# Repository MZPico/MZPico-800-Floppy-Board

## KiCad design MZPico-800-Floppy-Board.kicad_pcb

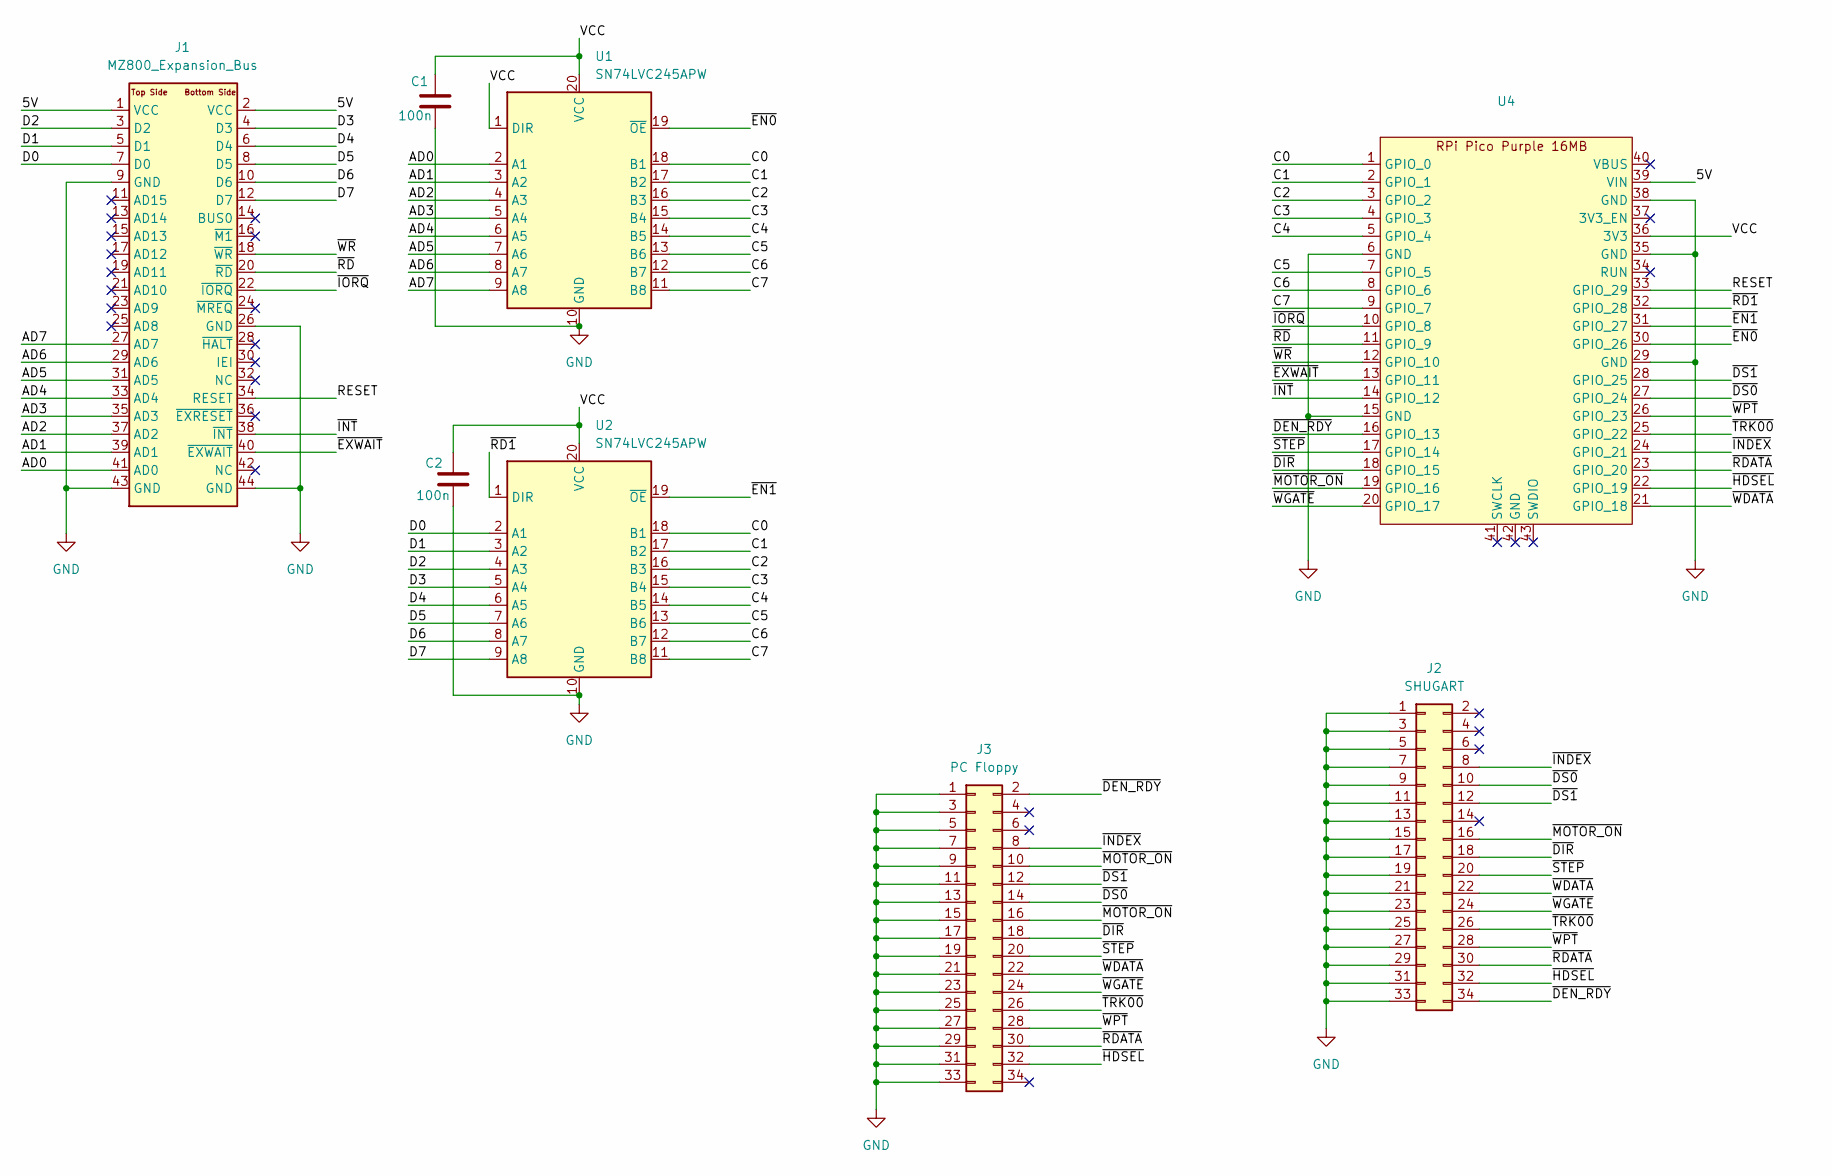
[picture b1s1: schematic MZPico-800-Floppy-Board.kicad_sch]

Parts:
C1, C2: 100n; C_0805_2012Metric
J1: MZ800_Expansion_Bus; MZ800_Expansion_Edge
J2: SHUGART; Floppy_Shugart_Edge
J3: PC Floppy; IDC-Header_2x17_P2.54mm_Horizontal
U1, U2: SN74LVC245APW; TSSOP-20_4.4x6.5mm_P0.65mm
U4: Pico_Purple_16MB

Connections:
/5V: J1.1 (VCC), J1.2 (VCC), U4.39 (VIN)
/AD0: J1.41 (AD0), U1.2 (A1)
/AD1: J1.39 (AD1), U1.3 (A2)
/AD2: J1.37 (AD2), U1.4 (A3)
/AD3: J1.35 (AD3), U1.5 (A4)
/AD4: J1.33 (AD4), U1.6 (A5)
/AD5: J1.31 (AD5), U1.7 (A6)
/AD6: J1.29 (AD6), U1.8 (A7)
/AD7: J1.27 (AD7), U1.9 (A8)
/C0: U1.18 (B1), U2.18 (B1), U4.1 (GPIO_0)
/C1: U1.17 (B2), U2.17 (B2), U4.2 (GPIO_1)
/C2: U1.16 (B3), U2.16 (B3), U4.3 (GPIO_2)
/C3: U1.15 (B4), U2.15 (B4), U4.4 (GPIO_3)
/C4: U1.14 (B5), U2.14 (B5), U4.5 (GPIO_4)
/C5: U1.13 (B6), U2.13 (B6), U4.7 (GPIO_5)
/C6: U1.12 (B7), U2.12 (B7), U4.8 (GPIO_6)
/C7: U1.11 (B8), U2.11 (B8), U4.9 (GPIO_7)
/D0: J1.7 (D0), U2.2 (A1)
/D1: J1.5 (D1), U2.3 (A2)
/D2: J1.3 (D2), U2.4 (A3)
/D3: J1.4 (D3), U2.5 (A4)
/D4: J1.6 (D4), U2.6 (A5)
/D5: J1.8 (D5), U2.7 (A6)
/D6: J1.10 (D6), U2.8 (A7)
/D7: J1.12 (D7), U2.9 (A8)
/RESET: J1.34 (RESET), U4.33 (GPIO_29)
/VCC: C1.1, C2.1, U1.1 (DIR), U1.20 (VCC), U2.20 (VCC), U4.36 (3V3)
/~DEN_RDY: J2.34, J3.2, U4.16 (GPIO_13)
/~DIR: J2.18, J3.18, U4.18 (GPIO_15)
/~DS0: J2.10, J3.14, U4.27 (GPIO_24)
/~DS1: J2.12, J3.12, U4.28 (GPIO_25)
/~EN0: U1.19 (~OE), U4.30 (GPIO_26)
/~EN1: U2.19 (~OE), U4.31 (GPIO_27)
/~EXWAIT: J1.40 (~EXWAIT), U4.13 (GPIO_11)
/~HDSEL: J2.32, J3.32, U4.22 (GPIO_19)
/~INDEX: J2.8, J3.8, U4.24 (GPIO_21)
/~INT: J1.38 (~INT), U4.14 (GPIO_12)
/~IORQ: J1.22 (~IORQ), U4.10 (GPIO_8)
/~MOTOR_ON: J2.16, J3.10, J3.16, U4.19 (GPIO_16)
/~RD1: U2.1 (DIR), U4.32 (GPIO_28)
/~RDATA: J2.30, J3.30, U4.23 (GPIO_20)
/~RD: J1.20 (~RD), U4.11 (GPIO_9)
/~STEP: J2.20, J3.20, U4.17 (GPIO_14)
/~TRK00: J2.26, J3.26, U4.25 (GPIO_22)
/~WDATA: J2.22, J3.22, U4.21 (GPIO_18)
/~WGATE: J2.24, J3.24, U4.20 (GPIO_17)
/~WPT: J2.28, J3.28, U4.26 (GPIO_23)
/~WR: J1.18 (~WR), U4.12 (GPIO_10)
GND: C1.2, C2.2, J1.9 (GND), J1.26 (GND), J1.43 (GND), J1.44 (GND), J2.1, J2.3, J2.5, J2.7, J2.9, J2.11, J2.13, J2.15, J2.17, J2.19, J2.21, J2.23, J2.25, J2.27, J2.29, J2.31, J2.33, J3.1, J3.3, J3.5, J3.7, J3.9, J3.11, J3.13, J3.15, J3.17, J3.19, J3.21, J3.23, J3.25, J3.27, J3.29, J3.31, J3.33, U1.10 (GND), U2.10 (GND), U4.6 (GND), U4.15 (GND), U4.29 (GND), U4.35 (GND), U4.38 (GND)

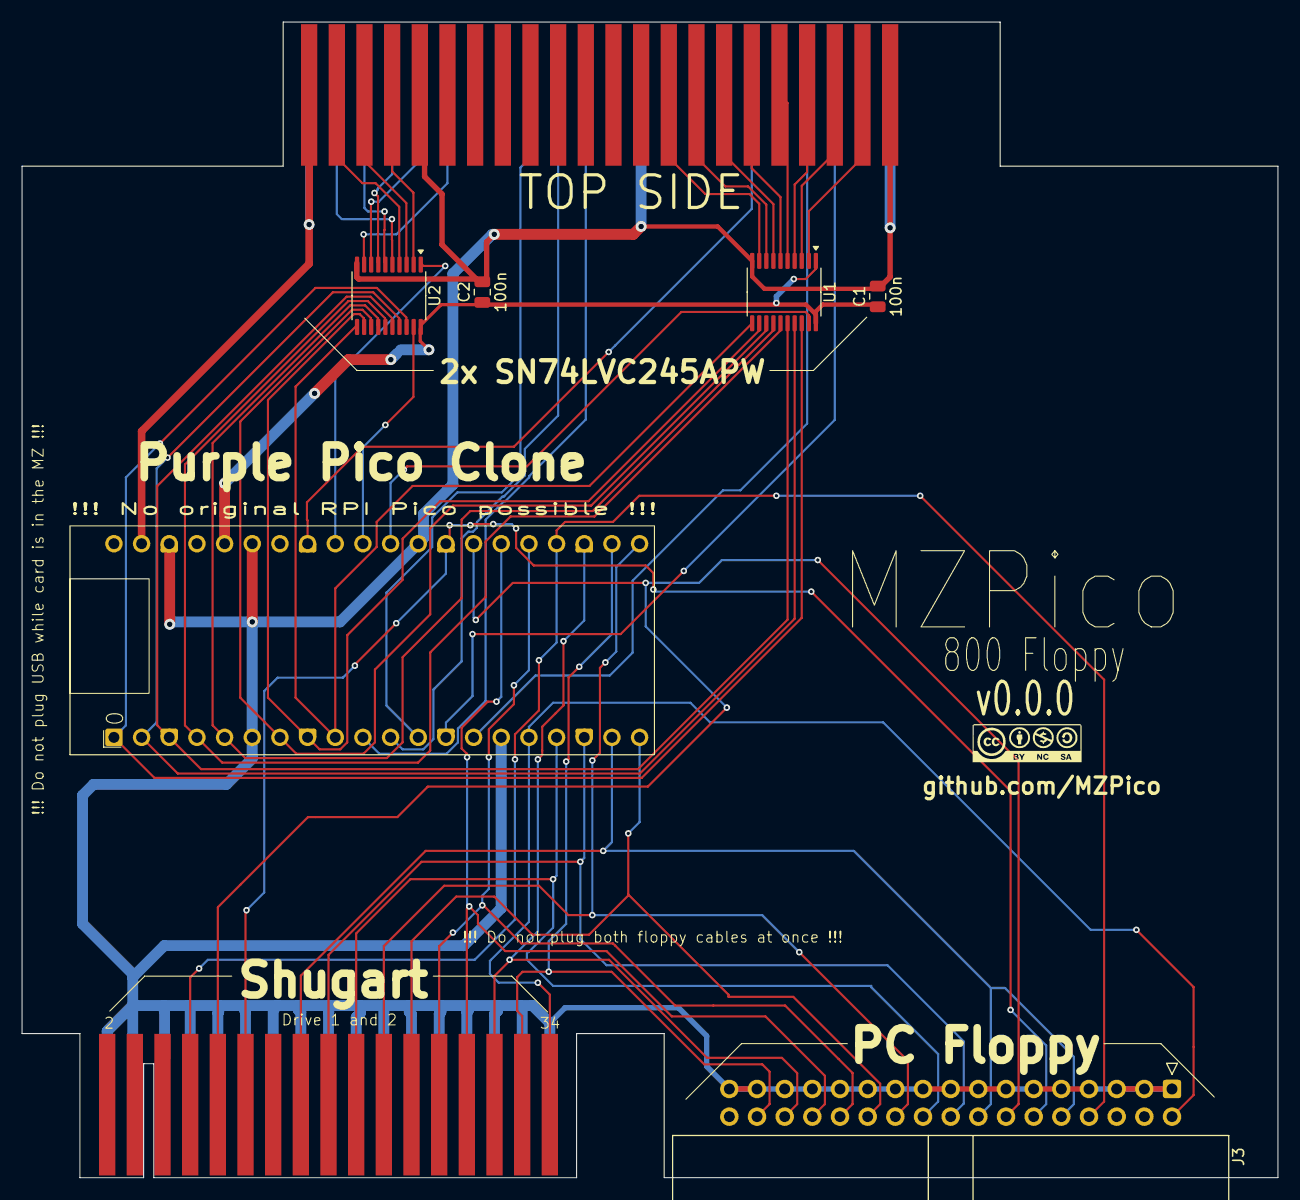
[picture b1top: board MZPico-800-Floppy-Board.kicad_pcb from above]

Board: 2 copper layers, 115.3 x 106.1 mm, 8 parts (1 on the bottom side), 49 nets.

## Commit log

2025-12-12 Initial version
2025-12-12 Adding github actions
2025-12-12 Adding submodules for footprints and symbols
2025-12-12 Addressing ERC
2025-12-12 Reset board version
2025-12-12 chore: update version on PCB to v0.0.1
